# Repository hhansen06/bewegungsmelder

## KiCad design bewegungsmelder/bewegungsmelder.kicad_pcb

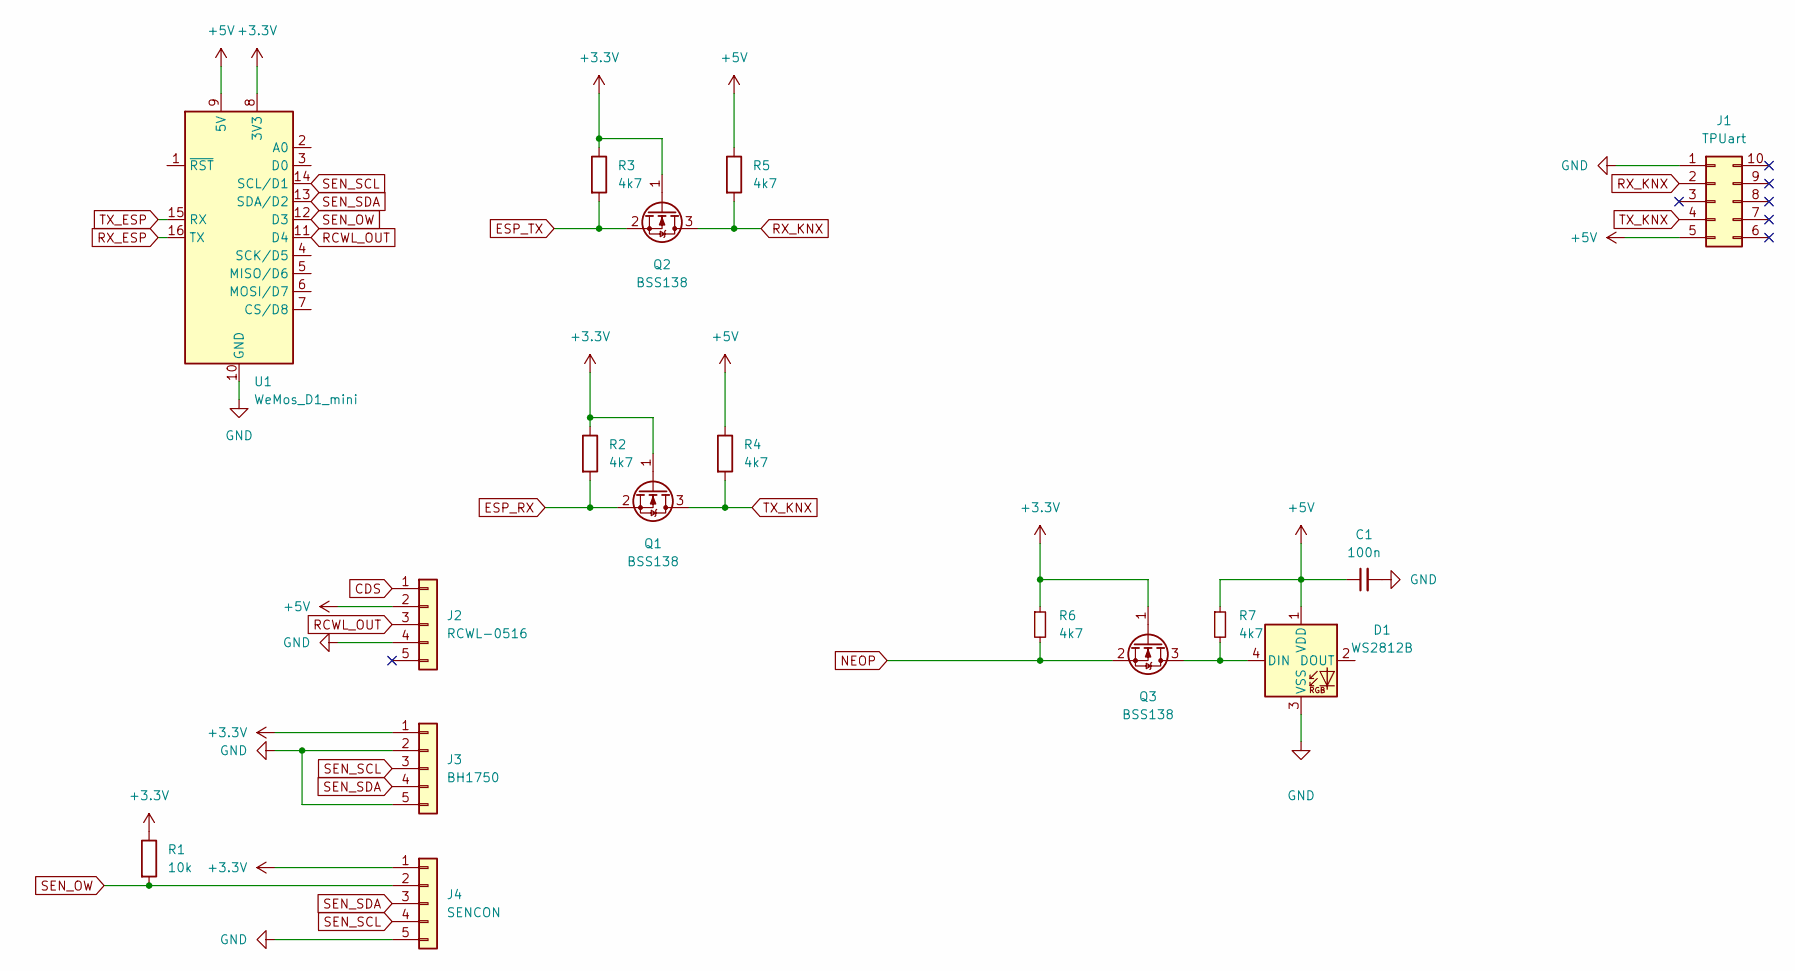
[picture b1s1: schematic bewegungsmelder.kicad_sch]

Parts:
C1: 100n; C_0603_1608Metric_Pad1.08x0.95mm_HandSolder
D1: WS2812B; LED_WS2812B_PLCC4_5.0x5.0mm_P3.2mm
J1: TPUart
J2: RCWL-0516; RCWL0516
J3: BH1750
J4: SENCON; PinHeader_1x05_P2.54mm_Vertical
Q1, Q2, Q3: BSS138; SOT-23
R1: 10k; R_0805_2012Metric_Pad1.20x1.40mm_HandSolder
R2, R3, R4, R5: 4k7; R_0805_2012Metric_Pad1.20x1.40mm_HandSolder
R6, R7: 4k7; C_0805_2012Metric_Pad1.18x1.45mm_HandSolder
U1: WeMos_D1_mini; WEMOS_D1_mini_light

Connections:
+3V3: J3.1, J4.1, Q1.1 (G), Q2.1 (G), Q3.1 (G), R1.1, R2.1, R3.1, R6.1, U1.8 (3V3)
+5V: C1.1, D1.1 (VDD), J1.5, J2.2, R4.1, R5.1, R7.1, U1.9 (5V)
CDS: J2.1
ESP_RX: Q1.2 (S), R2.2
ESP_TX: Q2.2 (S), R3.2
GND: C1.2, D1.3 (VSS), J1.1, J2.4, J3.2, J3.5, J4.5, U1.10 (GND)
NEOP: Q3.2 (S), R6.2
unnamed: D1.4 (DIN), Q3.3 (D), R7.2
RCWL_OUT: J2.3, U1.11 (D4)
RX_ESP: U1.16 (TX)
RX_KNX: J1.2, Q2.3 (D), R5.2
SEN_OW: J4.2, R1.2, U1.12 (D3)
SEN_SCL: J3.3, J4.4, U1.14 (SCL/D1)
SEN_SDA: J3.4, J4.3, U1.13 (SDA/D2)
TX_ESP: U1.15 (RX)
TX_KNX: J1.4, Q1.3 (D), R4.2

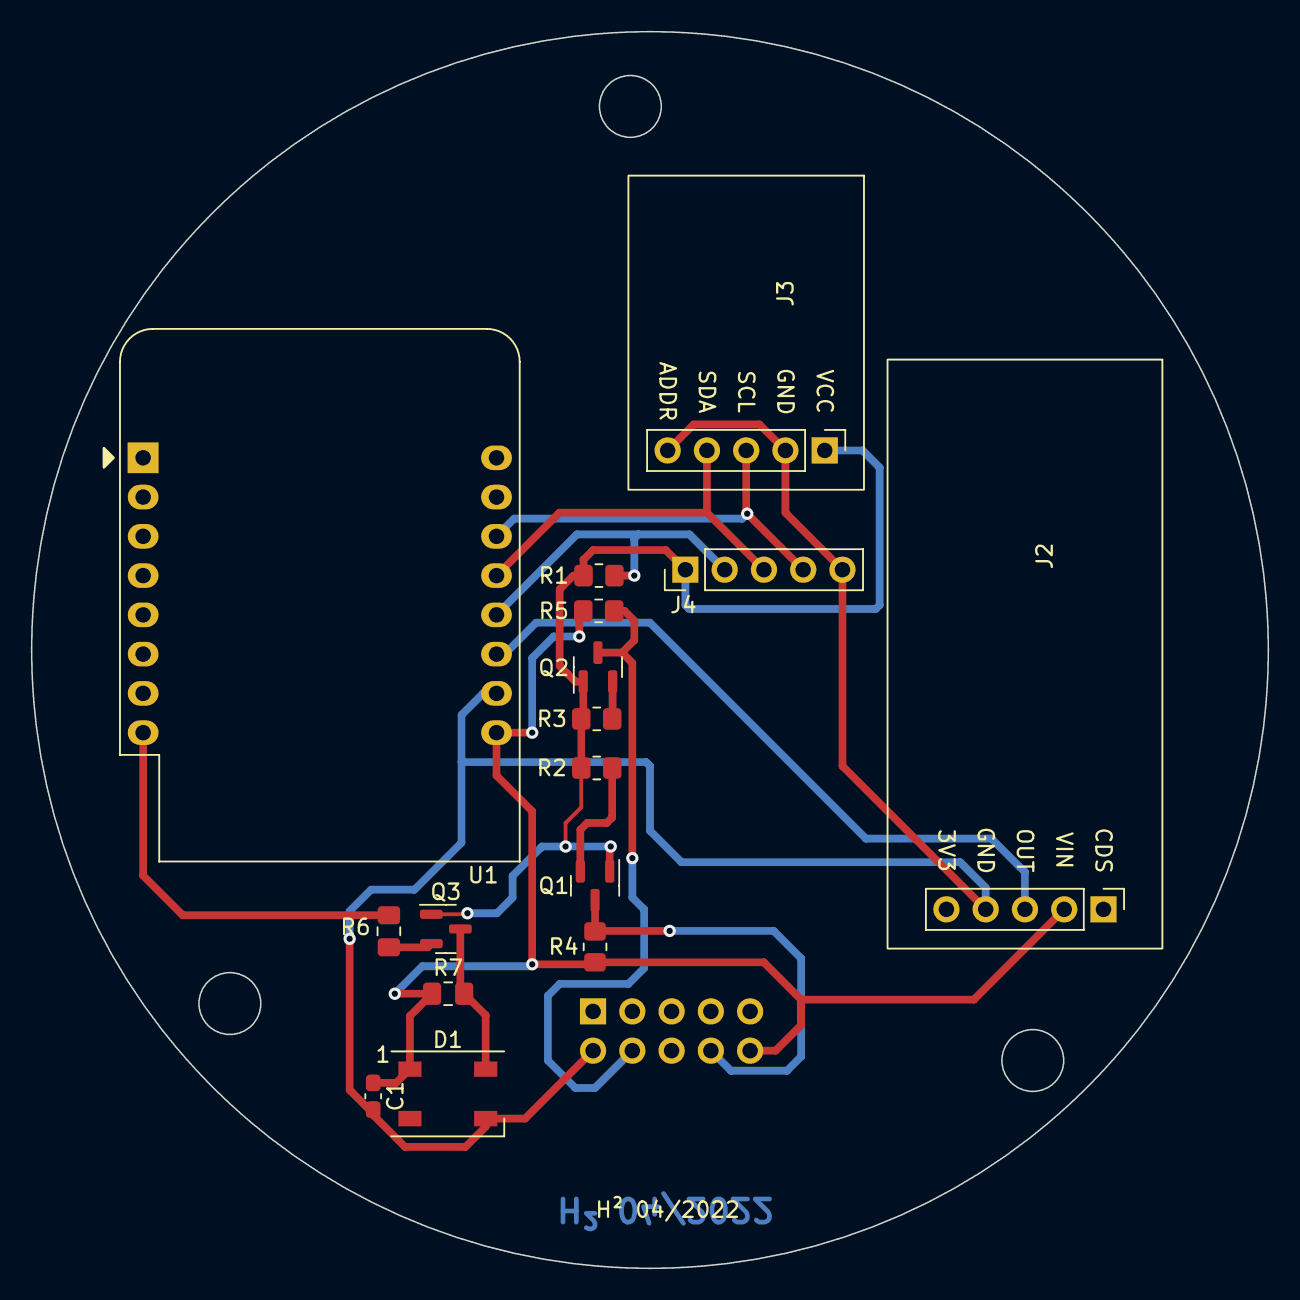
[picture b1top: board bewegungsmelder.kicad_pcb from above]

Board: 2 copper layers, 80.0 x 80.0 mm, 17 parts (1 on the bottom side), 13 nets.

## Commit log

2022-04-17 init
